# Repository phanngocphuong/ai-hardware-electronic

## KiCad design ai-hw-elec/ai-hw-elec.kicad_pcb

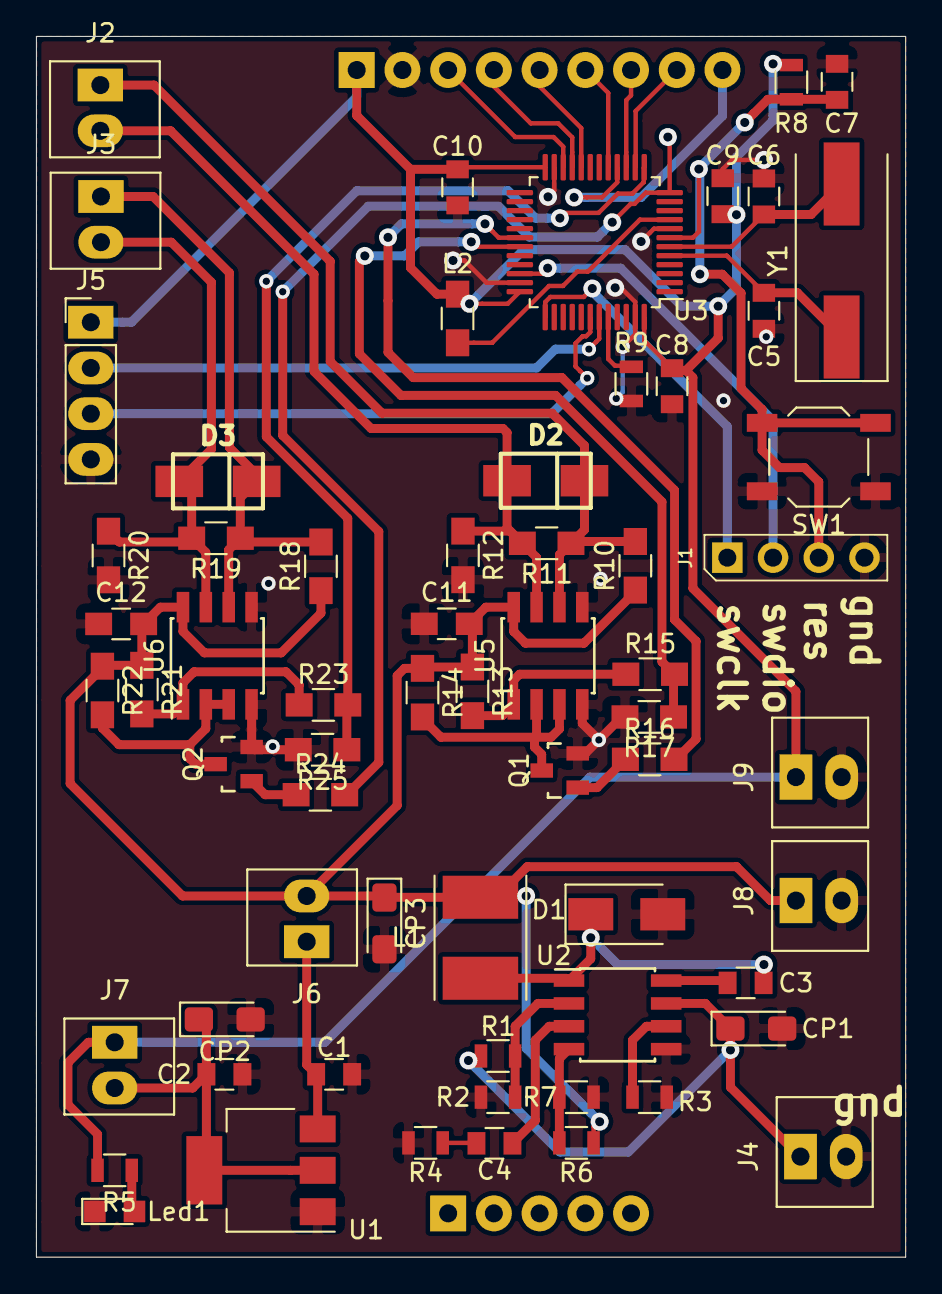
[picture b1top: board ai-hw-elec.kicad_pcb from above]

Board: 2 copper layers, 48.3 x 67.8 mm, 65 parts (1 on the bottom side), 44 nets.

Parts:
C1, C2, C3, C7, C8, C9, C10: 104; C_0805
C4: 150p; C_0805
C5, C6: 15p; C_0805
C11, C12: 104; C_0805_HandSoldering
CP1, CP2: 10uF; CP_Tatanlum_1206_3216
CP3: 20uF; CP_Tatanlum_1206_3216
D1: SS3x_SMA; D_SMA
D2, D3: D_TVS; DO-214AC(SMA)
J1: Conn_Progam_Stm; Conn_Program
J2: RS485_uart1; Header-2pin-2.54-white
J3: RS485_uart2; Header-2pin-2.54-white
J4, J8, J9: Conn_01x02_power; Header-2pin-2.54-white
J5: I2C_Port; Header-4pin-2.54
J6: 5v lock; Header-2pin-2.54-white
J7: 3v3 lock; Header-2pin-2.54-white
L1: L_5D28; L_5D28_HandSoldering
L2: 30ohm; L_0805_HandSoldering
Led1: Led_0805; LED_0805
Q1, Q2: C1815_SOT23; SOT-23
R1, R4: 100k; R_0805
R2: 24.9k; R_0805
R3: 62k; R_0805
R5: 1k; R_0805
R6: 210k; R_0805
R7: 40.2k; R_0805
R8, R9: 10k; R_0805
R10, R12, R18, R20: 10K; R_0805_HandSoldering
R11, R16, R19, R24: 2.2k; R_0805_HandSoldering
R13, R14, R17, R21, R22, R25: 10k; R_0805_HandSoldering
R15, R23: 4k7; R_0805_HandSoldering
SW1: Button_Push_TL3342; BUTTON_TL3342
U1: ASM1117-3V3; SOT-223
U2: MP1584; SOIC-8_3.9x4.9mm_Pitch1.27mm
U3: Stm32f103c8x; LQFP-48_7x7mm_P0.5mm
U4: LCD_ILI9341_2.2inch
U5, U6: MAX485_SMD; SOIC-8_3.9x4.9mm_Pitch1.27mm
Y1: Crystal-Mhz; Crystal_HC49-S

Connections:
3V3: C8.1, C9.1, C10.1, J5.1, J7.1, J9.1, L2.1, R5.1, R8.1, U3.24, U3.36, U3.48, U4.1
5v: C11.2, C12.2, CP3.1, J6.2, J8.1, L1.2, R6.1, R10.1, R13.1, R14.1, R18.1, R21.1, R22.1, U5.8, U6.8
12v: CP1.1, J4.1, R1.1, U2.7
/CS: U3.22, U4.3
/LCD-CLK: U3.15, U4.7
/LCD-MISO: U3.16, U4.9
/LCD-MOSI: U3.17, U4.6
/LED: U3.14, U4.8
/RESET: U3.21, U4.4
/RS: U3.20, U4.5
/Stm32f103c8tx/SWCLK: J1.1, U3.37
/Stm32f103c8tx/SWDIO: J1.2, U3.34
/Stm32f103c8tx/i2c1_scl: J5.3, U3.42
/Stm32f103c8tx/i2c1_sda: J5.2, U3.43
/Stm32f103c8tx/osc1: C5.1, U3.5, Y1.1
/Stm32f103c8tx/osc2: C6.1, U3.6, Y1.2
/Stm32f103c8tx/res: C7.1, J1.3, R8.2, SW1.2, U3.7
/rs485uart1/A: D2.1, J2.1, R10.2, R11.1, U5.6
/rs485uart1/B: D2.2, J2.2, R11.2, R12.1, U5.7
/rs485uart1/RS485-RX: R15.2, R17.1, U3.31
/rs485uart1/RS485-TX: R16.2, U3.30
/rs485uart2/A: D3.1, J3.1, R18.2, R19.1, U6.6
/rs485uart2/B: D3.2, J3.2, R19.2, R20.1, U6.7
/rs485uart2/RS485-RX: R23.2, R25.1, U3.13
/rs485uart2/RS485-TX: R24.2, U3.12
GND: C1.2, C2.2, C5.2, C6.2, C7.2, C8.2, C9.2, C10.2, C11.1, C12.1, CP1.2, CP2.2, CP3.2, D1.2, J1.4, J4.2, J5.4, J8.2, J9.2, Led1.1, Q1.2, Q2.2, R2.2, R3.2, R4.2, R7.2, R9.2, R12.2, R17.2, R20.2, R25.2, SW1.1, U1.1, U2.5, U3.8, U3.23, U3.35, U3.47, U4.2, U5.4, U5.5, U6.4, U6.5
unnamed: C1.1, J6.1, U1.3
unnamed: C2.1, CP2.1, J7.2, U1.2, U1.4
unnamed: C3.1, U2.8
unnamed: C3.2, D1.1, L1.1, U2.1
unnamed: C4.1, U2.3
unnamed: C4.2, R4.1
unnamed: L2.2, U3.9
unnamed: Led1.2, R5.2
unnamed: Q1.1, R16.1
unnamed: Q1.3, R14.2, U5.2, U5.3
unnamed: Q2.1, R24.1
unnamed: Q2.3, R22.2, U6.2, U6.3
unnamed: R1.2, R2.1, U2.2
unnamed: R3.1, U2.6
unnamed: R6.2, R7.1, U2.4
unnamed: R9.1, U3.44
unnamed: R13.2, R15.1, U5.1
unnamed: R21.2, R23.1, U6.1
